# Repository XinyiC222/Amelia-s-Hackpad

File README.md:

# Amelia-s-Hackpad

My personal Macropad that would help me open up apps, turn volume up and down, and do other cool things. I am using: 4 SW_Push, and 1 rotary encoder, 2 neopixels, and a Seed XIAO RP2040. This also uses KMK firmware.

<h1>FEATURES:</h1>

- 1x EC11 Rotary Encoder
- 4x Keys
- 2x SK6812 MINI-E LED

<h1>BOM:</h1>

- 1x Seeed XIAO RP2040
- 1x EC11 Rotary Encoder
- 4x Cherry MX Swithces
- 4x DSA Keycaps
- 2x SK6812 MINI-E LED
- 4x M3 Hex Steel nuts
- 1x Case (two 3d printed parts, top and bottom)

Here is my final designs!

<h1>PCB:</h1>
<p>I used KiCad to make my PCB board. The silkscreen is just random unicodes I found!! </p>

<p>Schematic:</p>

<p>PCB:</p>

<h1>CAD</h1>
<p>I added a bit of tilt to make it easy to use.</p>

<h1>Firmware:</h1>

This macropad uses KMK.
- The rotary encoder changes the volume and mutes/unmutes.
- The 4 keys opens different apps by using spotlight search(MAC)
- The mini LED is green when you turn it the device on, then it slowly fades in and out.

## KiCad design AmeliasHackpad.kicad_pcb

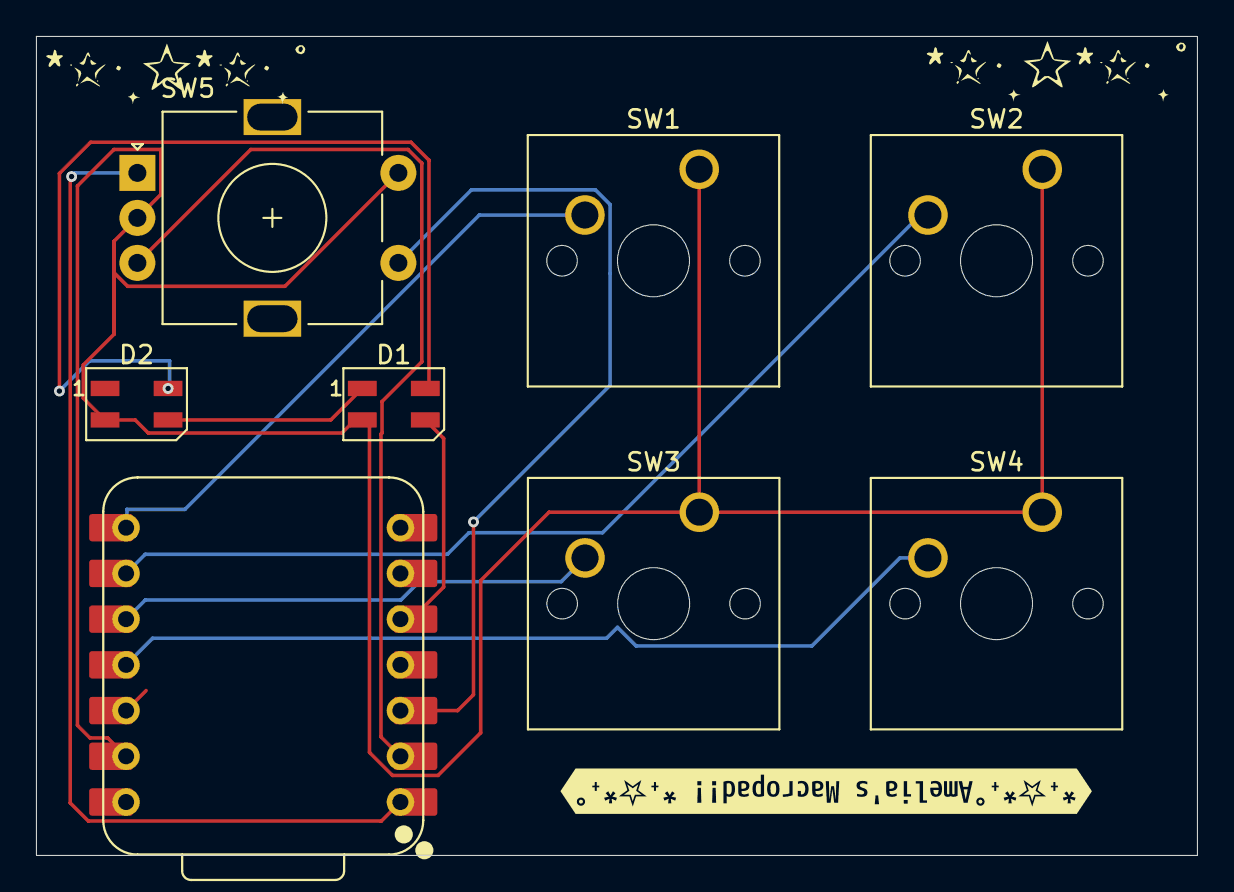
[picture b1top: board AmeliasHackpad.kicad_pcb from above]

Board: 2 copper layers, 64.5 x 45.5 mm, 9 parts (0 on the bottom side), 11 nets.

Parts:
D1, D2: SK6812MINI; LED_SK6812MINI_PLCC4_3.5x3.5mm_P1.75mm
SW1, SW2, SW3, SW4: SW_Push; SW_Cherry_MX_1.00u_PCB
SW5: RotaryEncoder_Switch; RotaryEncoder_Alps_EC11E-Switch_Vertical_H20mm
U1: XIAO-RP2040-DIP
kibuzzard-693A5F78: G***; kibuzzard-693A5F78

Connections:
5V: D1.4 (VDD), D2.4 (VDD)
GND: D1.2 (VSS), D2.2 (VSS), SW1.1, SW2.1, SW3.1, SW4.1, SW5.C, SW5.S2, U1.13 (GND)
unnamed: D1.3 (DIN), U1.5 (GPIO6/SDA)
unnamed: D1.1 (DOUT), D2.3 (DIN)
unnamed: SW1.2, U1.8 (GPIO1/RX)
unnamed: SW2.2, U1.9 (GPIO2/SCK)
unnamed: SW4.2, U1.11 (GPIO3/MOSI)
unnamed: SW3.2, U1.10 (GPIO4/MISO)
unnamed: SW5.A, U1.1 (GPIO26/ADC0/A0)
unnamed: SW5.B, U1.2 (GPIO27/ADC1/A1)
unnamed: SW5.S1, U1.3 (GPIO28/ADC2/A2)

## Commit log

2025-12-10 12/09/2025 worked for around 2 hours figuring out how to add the OPL library(footprint, and symbols), draw the schematic and started PCB board. It is super fun, hope to finish by the end of the week!
2025-12-10 Tried agian… restarted
2025-12-13 Updated Macropad and added a rotary encoder
2025-12-13 Rotated PCB
2025-12-13 Update README with project details
    Added a project description to the README.
2025-12-13 added the 3d files
2025-12-13 added 3d models
2025-12-13 grouped into folders and updated CAD file
2025-12-13 Update README with BOM and design schematics
    Added a Bill of Materials (BOM) and design images.
2025-12-13 Format section headers in README.md
2025-12-14 Enhance README with features and BOM details
    Updated README to include KMK firmware and detailed BOM.
2025-12-14 Fix HTML formatting in README.md
2025-12-14 Revise features section in README
    Updated features list in README to reflect current components.
2025-12-14 changed 3d model
2025-12-14 changed CAD
2025-12-14 added code
2025-12-14 changed code name to Main
2025-12-15 added PCB gerber files
